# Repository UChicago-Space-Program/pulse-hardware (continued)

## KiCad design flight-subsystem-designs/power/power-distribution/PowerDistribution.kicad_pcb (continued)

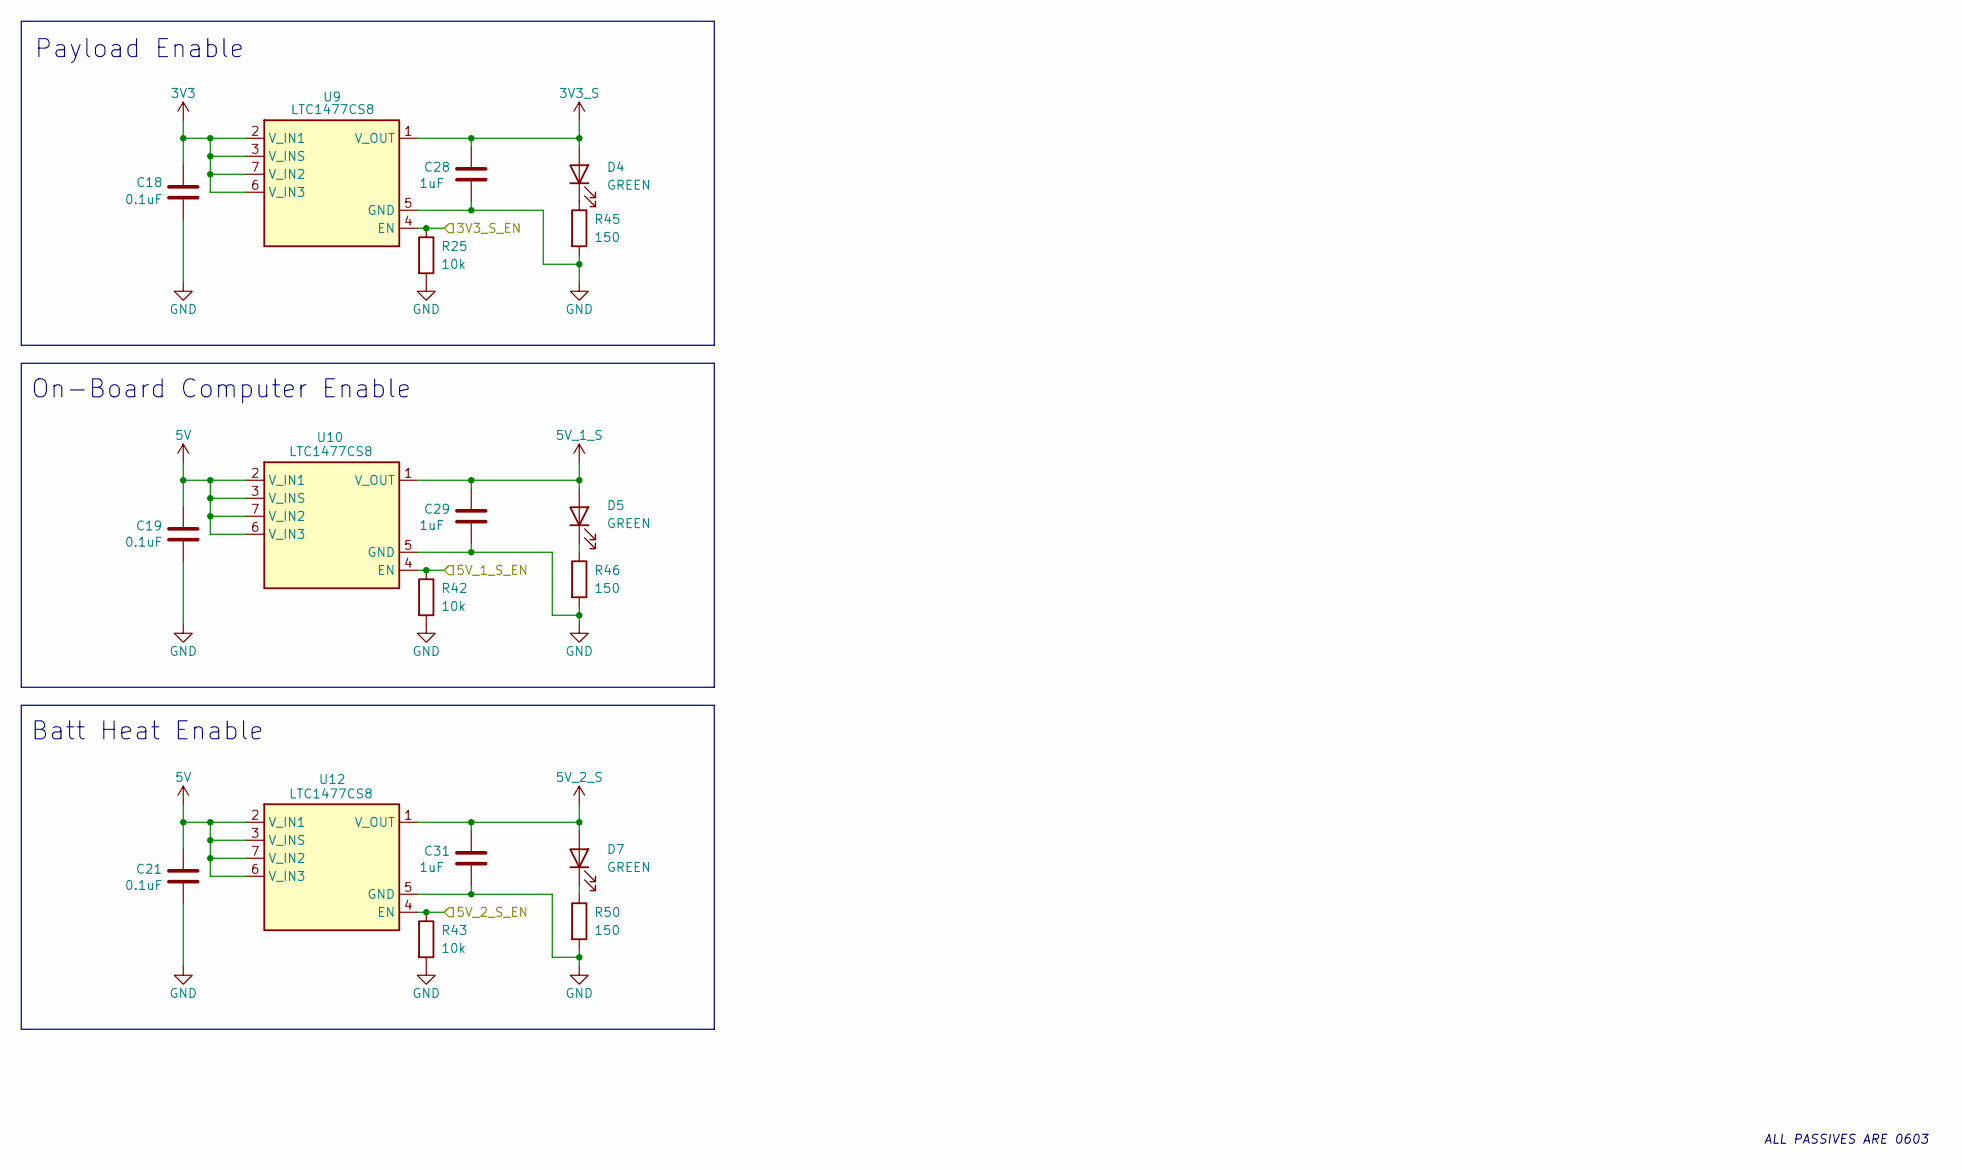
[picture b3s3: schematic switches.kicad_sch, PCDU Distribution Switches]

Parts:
C18, C19, C21: 0.1uF; C_0603_1608Metric
C28, C29, C31: 1uF; C_0603_1608Metric
D4, D5, D7: GREEN; LED_0603_1608Metric
R25, R42, R43: 10k; R_0603_1608Metric
R45, R46, R50: 150; R_0603_1608Metric
U9, U10, U12: LTC1477CS8; SOIC-8_3.9x4.9mm_P1.27mm

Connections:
3V3: C18.1, U9.2 (V_IN1), U9.3 (V_INS), U9.6 (V_IN3), U9.7 (V_IN2); also elsewhere on the board
3V3_S: C28.1, D4.2 (A), U9.1 (V_OUT), U9.8 (V_OUT); also elsewhere on the board
5V: C19.1, C21.1, U10.2 (V_IN1), U10.3 (V_INS), U10.6 (V_IN3), U10.7 (V_IN2), U12.2 (V_IN1), U12.3 (V_INS), U12.6 (V_IN3), U12.7 (V_IN2); also elsewhere on the board
5V_1_S: C29.1, D5.2 (A), U10.1 (V_OUT), U10.8 (V_OUT); also elsewhere on the board
5V_2_S: C31.1, D7.2 (A), U12.1 (V_OUT), U12.8 (V_OUT); also elsewhere on the board
/Control/3V3_S_EN: R25.1, U9.4 (EN); also elsewhere on the board
/Control/5V_1_S_EN: R42.1, U10.4 (EN); also elsewhere on the board
/Control/5V_2_S_EN: R43.1, U12.4 (EN); also elsewhere on the board
GND: C18.2, C19.2, C21.2, C28.2, C29.2, C31.2, R25.2, R42.2, R43.2, R45.2, R46.2, R50.2, U9.5 (GND), U10.5 (GND), U12.5 (GND); also elsewhere on the board
unnamed: D4.1 (K), R45.1
unnamed: D5.1 (K), R46.1
unnamed: D7.1 (K), R50.1

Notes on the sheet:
Payload Enable
Batt Heat Enable
ALL PASSIVES ARE 0603
On-Board Computer Enable

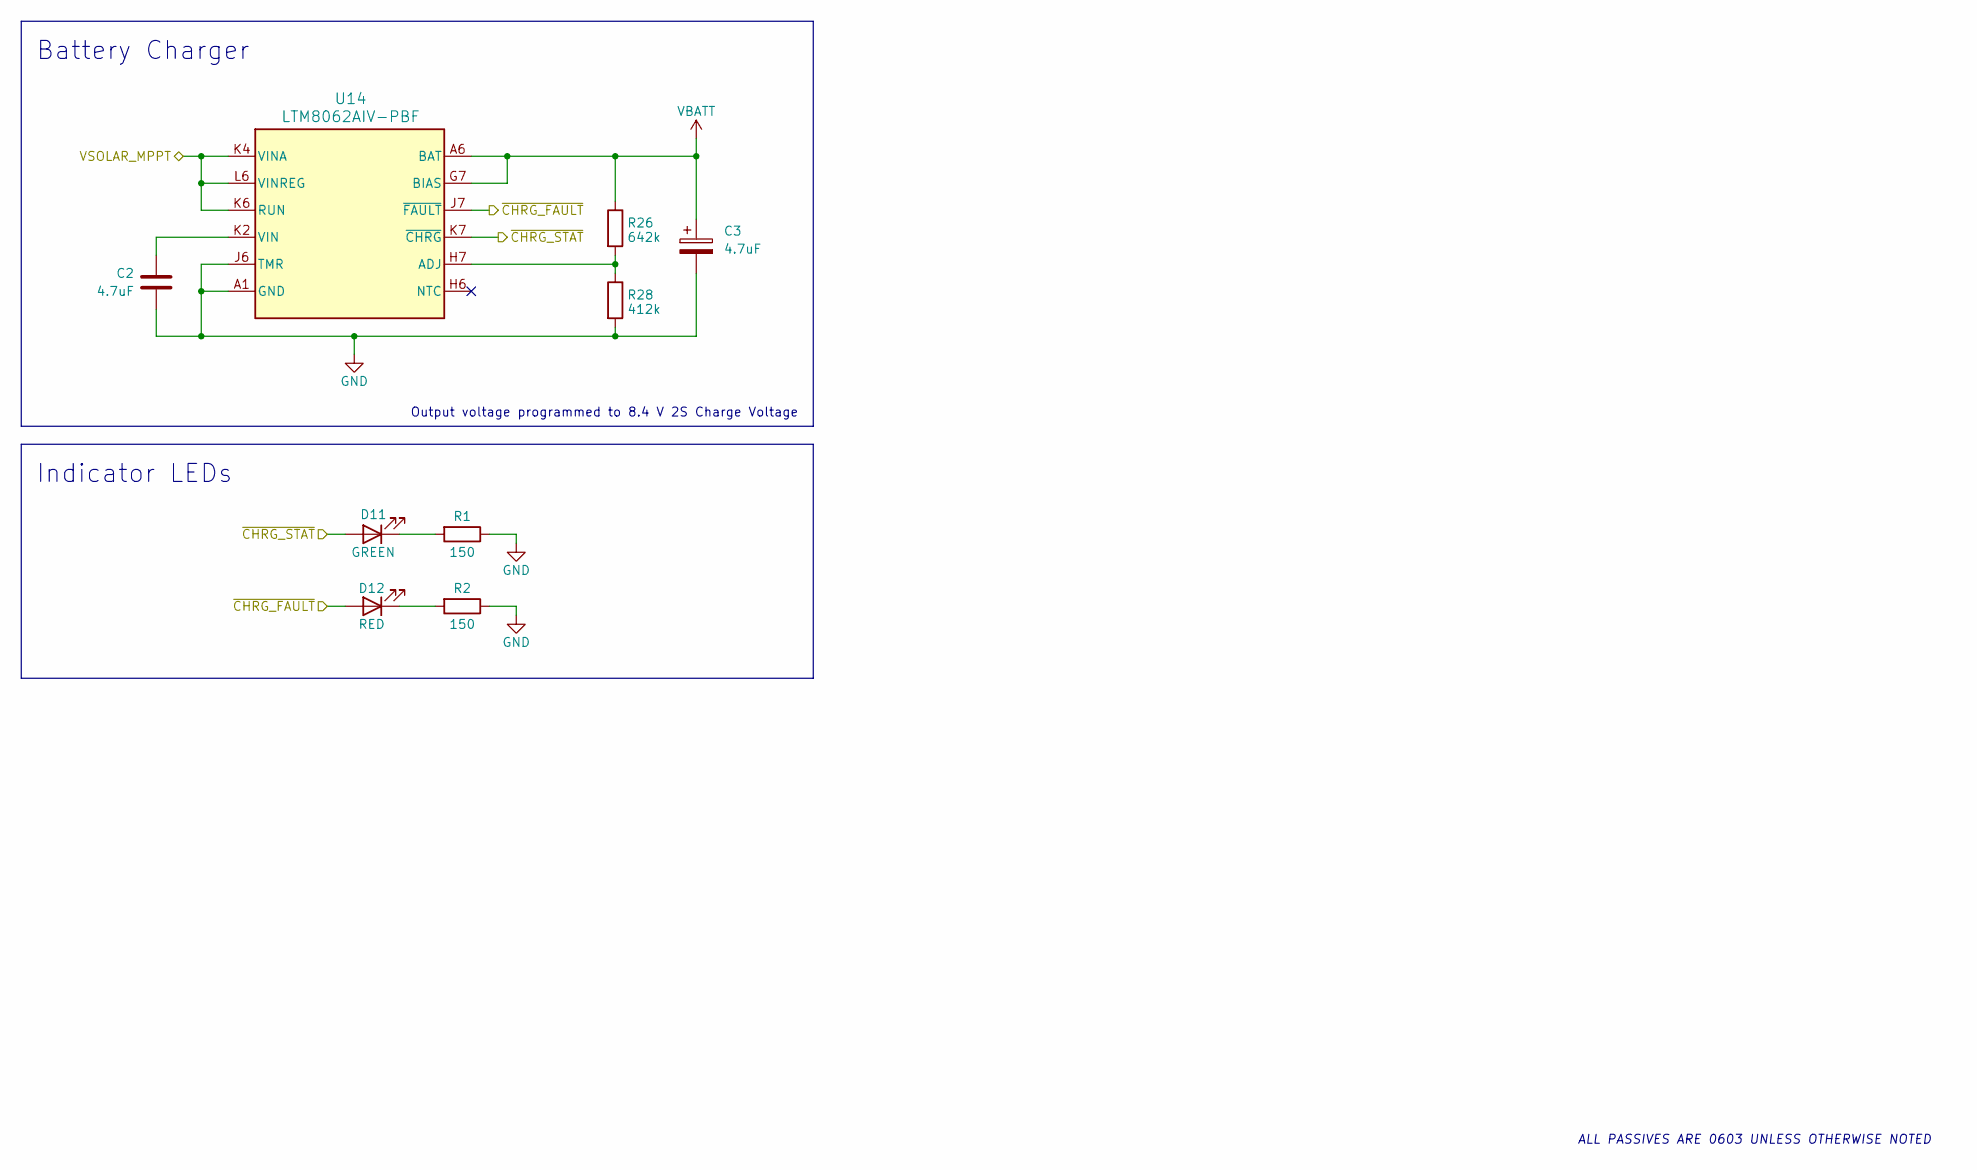
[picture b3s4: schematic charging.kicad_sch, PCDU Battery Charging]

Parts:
C2: 4.7uF; C_1206_3216Metric
C3: 4.7uF; CP_EIA-3528-12_Kemet-T
D11: GREEN; LED_0603_1608Metric
D12: RED; LED_0603_1608Metric
R1, R2: 150; R_0603_1608Metric
R26: 642k; R_0603_1608Metric
R28: 412k; R_0603_1608Metric
U14: LTM8062AIV-PBF; LGA-77_15X9_2_LIT

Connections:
/Charging/~CHRG_FAULT: D12.2 (A), U14.J7 (~FAULT); also elsewhere on the board
/Charging/~CHRG_STAT: D11.2 (A), U14.K7 (~CHRG); also elsewhere on the board
GND: C2.1, C3.2, R1.1, R2.1, R28.2, U14.A1 (GND), U14.A2 (GND), U14.A3 (GND), U14.A4 (GND), U14.A5 (GND), U14.B1 (GND), U14.B2 (GND), U14.B3 (GND), U14.B5 (GND), U14.C1 (GND), U14.C2 (GND), U14.C3 (GND), U14.C4 (GND), U14.C5 (GND), U14.D1 (GND), U14.D2 (GND), U14.D3 (GND), U14.D4 (GND), U14.D5 (GND), U14.F1 (GND), U14.F2 (GND), U14.F3 (GND), U14.F4 (GND), U14.F5 (GND), U14.G1 (GND), U14.G2 (GND), U14.G3 (GND), U14.G4 (GND), U14.G5 (GND), U14.G6 (GND), U14.H1 (GND), U14.H2 (GND), U14.H3 (GND), U14.H4 (GND), U14.H5 (GND), U14.J1 (GND), U14.J2 (GND), U14.J3 (GND), U14.J4 (GND), U14.J5 (GND), U14.J6 (TMR), U14.L7 (GND); also elsewhere on the board
unnamed: C2.2, U14.K1 (VIN), U14.K2 (VIN), U14.K3 (VIN), U14.L1 (VIN), U14.L2 (VIN), U14.L3 (VIN)
unnamed: D11.1 (K), R1.2
unnamed: D12.1 (K), R2.2
unnamed: R26.2, R28.1, U14.H7 (ADJ)
VBATT: C3.1, R26.1, U14.A6 (BAT), U14.A7 (BAT), U14.B6 (BAT), U14.B7 (BAT), U14.C6 (BAT), U14.C7 (BAT), U14.D6 (BAT), U14.D7 (BAT), U14.E6 (BAT), U14.E7 (BAT), U14.F6 (BAT), U14.F7 (BAT), U14.G7 (BIAS); also elsewhere on the board
VINA: U14.K4 (VINA), U14.K5 (VINA), U14.K6 (RUN), U14.L4 (VINA), U14.L5 (VINA), U14.L6 (VINREG); also elsewhere on the board

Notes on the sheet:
ALL PASSIVES ARE 0603 UNLESS OTHERWISE NOTED
Battery Charger
Indicator LEDs
Output voltage programmed to 8.4 V 2S Charge Voltage

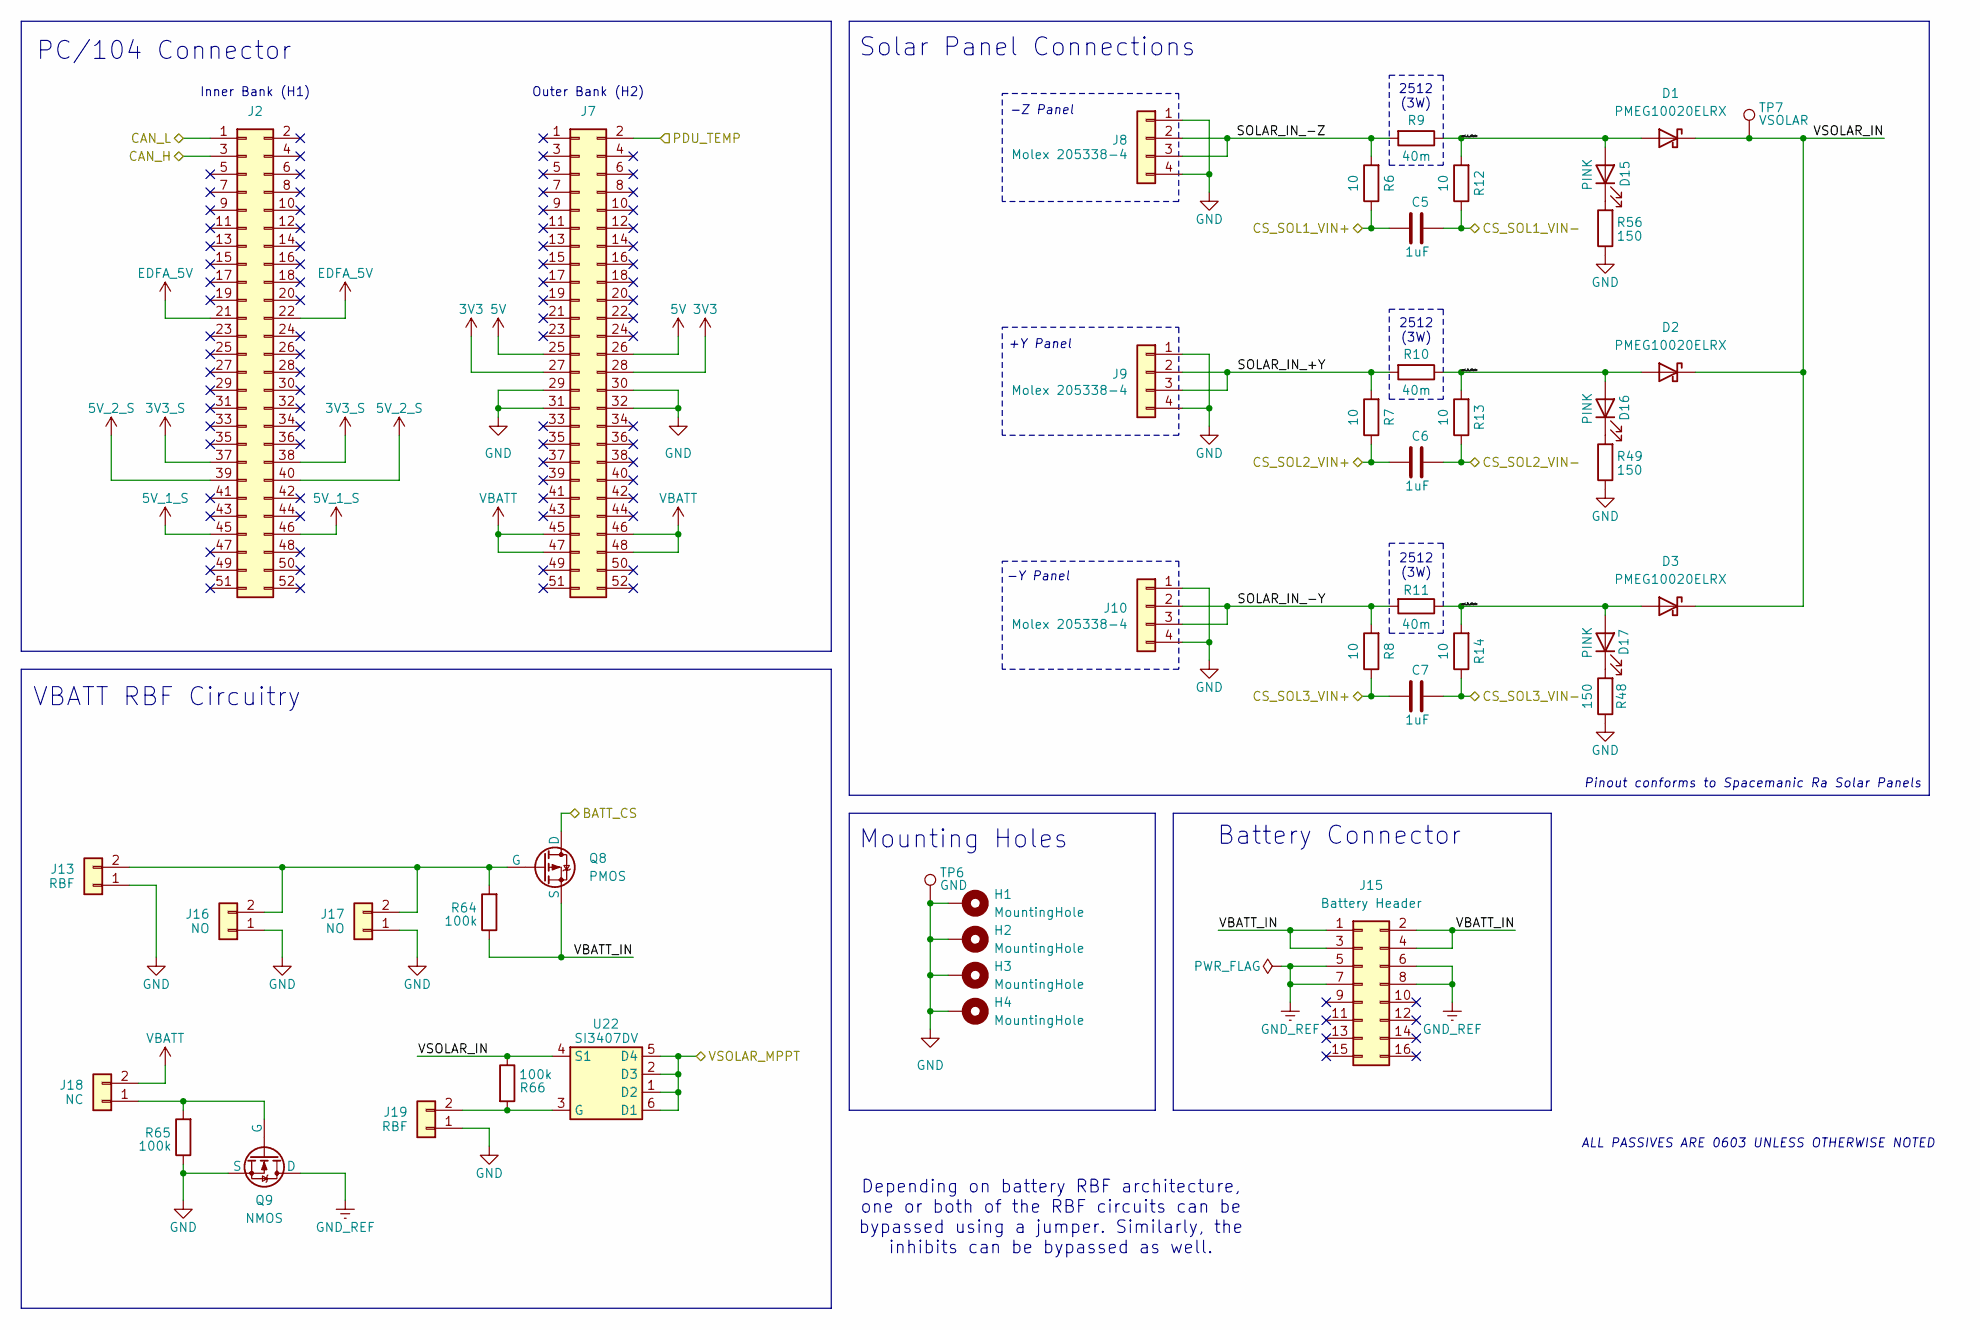
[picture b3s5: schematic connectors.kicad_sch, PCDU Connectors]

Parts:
C5, C6, C7: 1uF; C_0603_1608Metric
D1, D2, D3: PMEG10020ELRX; Nexperia_CFP3_SOD-123W
D15, D16, D17: PINK; LED_0603_1608Metric
H1, H2, H3, H4: MountingHole; MountingHole_3.2mm_M3_Pad_TopBottom
J2, J7: Conn_02x26_Odd_Even; PinHeader_2x26_P2.54mm_Vertical
J8, J9, J10: Molex 205338-4; Molex_PicoBlade_53047-0410_1x04_P1.25mm_Vertical
J13, J19: RBF; Molex_PicoBlade_53047-0210_1x02_P1.25mm_Vertical
J15: Battery Header; PinHeader_2x08_P2.54mm_Vertical
J16, J17: NO; Molex_PicoBlade_53047-0210_1x02_P1.25mm_Vertical
J18: NC; Molex_PicoBlade_53047-0210_1x02_P1.25mm_Vertical
Q8: PMOS; TSOP-6_1.65x3.05mm_P0.95mm
Q9: NMOS; TSOP-6_1.65x3.05mm_P0.95mm
R6, R7, R8, R12, R13, R14: 10; R_0603_1608Metric
R9, R10, R11: 40m; R_2512_6332Metric
R48, R49, R56: 150; R_0603_1608Metric
R64, R65, R66: 100k; R_0603_1608Metric
TP6: GND; TestPoint_Keystone_5000-5004_Miniature
TP7: VSOLAR; TestPoint_Keystone_5000-5004_Miniature
U22: SI3407DV; TSOP-6_1.65x3.05mm_P0.95mm

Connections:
3V3: J7.27, J7.28; also elsewhere on the board
3V3_S: J2.37, J2.38; also elsewhere on the board
5V: J7.25, J7.26; also elsewhere on the board
5V_1_S: J2.45, J2.46; also elsewhere on the board
5V_2_S: J2.39, J2.40; also elsewhere on the board
/Connectors/BATT_CS: Q8.1 (D), Q8.2 (D), Q8.5 (D), Q8.6 (D); also elsewhere on the board
/Connectors/CAN_H: J2.3; also elsewhere on the board
/Connectors/CAN_L: J2.1; also elsewhere on the board
/Connectors/CS_SOL1_VIN+: C5.2, R6.1; also elsewhere on the board
/Connectors/CS_SOL1_VIN-: C5.1, R12.1; also elsewhere on the board
/Connectors/CS_SOL2_VIN+: C6.2, R7.1; also elsewhere on the board
/Connectors/CS_SOL2_VIN-: C6.1, R13.1; also elsewhere on the board
/Connectors/CS_SOL3_VIN+: C7.2, R8.1; also elsewhere on the board
/Connectors/CS_SOL3_VIN-: C7.1, R14.1; also elsewhere on the board
/Connectors/PDU_TEMP: J7.2; also elsewhere on the board
/Connectors/SOLAR_IN_+Y: J9.2, J9.3, R7.2, R10.2
/Connectors/SOLAR_IN_-Y: J10.2, J10.3, R8.2, R11.2
/Connectors/SOLAR_IN_-Z: J8.2, J8.3, R6.2, R9.2
/Connectors/VBATT_IN: J15.1, J15.2, J15.3, J15.4, Q8.4 (S), R64.1
/Connectors/VSOLAR_IN: D1.1 (K), D2.1 (K), D3.1 (K), R66.1, TP7.1, U22.4 (S1)
/Connectors/sol_1_diode: D1.2 (A), D15.2 (A), R9.1, R12.2
/Connectors/sol_2_diode: D2.2 (A), D16.2 (A), R10.1, R13.2
/Connectors/sol_3_diode: D3.2 (A), D17.2 (A), R11.1, R14.2
EDFA_5V: J2.21, J2.22; also elsewhere on the board
GND: H1.MP, H2.MP, H3.MP, H4.MP, J7.29, J7.30, J7.31, J7.32, J8.1, J8.4, J9.1, J9.4, J10.1, J10.4, J13.1, J16.1, J17.1, J19.1, Q9.3 (S), R48.1, R49.1, R56.1, R65.1, TP6.1; also elsewhere on the board
GND_REF: J15.5, J15.6, J15.7, J15.8, Q9.1 (D)
unnamed: D15.1 (K), R56.2
unnamed: D16.1 (K), R49.2
unnamed: D17.1 (K), R48.2
unnamed: J13.2, J16.2, J17.2, Q8.3 (G), R64.2
unnamed: J18.1, Q9.2 (G), R65.2
unnamed: J19.2, R66.2, U22.3 (G)
VBATT: J7.45, J7.46, J7.47, J7.48, J18.2; also elsewhere on the board
VINA: U22.1 (D2), U22.2 (D3), U22.5 (D4), U22.6 (D1); also elsewhere on the board

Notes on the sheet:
2512 (3W)
PC/104 Connector
Inner Bank (H1)
-Z Panel
Mounting Holes
Solar Panel Connections
Pinout conforms to Spacemanic Ra Solar Panels
+Y Panel
-Y Panel
Battery Connector
VBATT RBF Circuitry
ALL PASSIVES ARE 0603 UNLESS OTHERWISE NOTED
Depending on battery RBF architecture, one or both of the RBF circuits can be bypassed using a jumper. Similarly, the inhibits can be bypassed as well.
Outer Bank (H2)

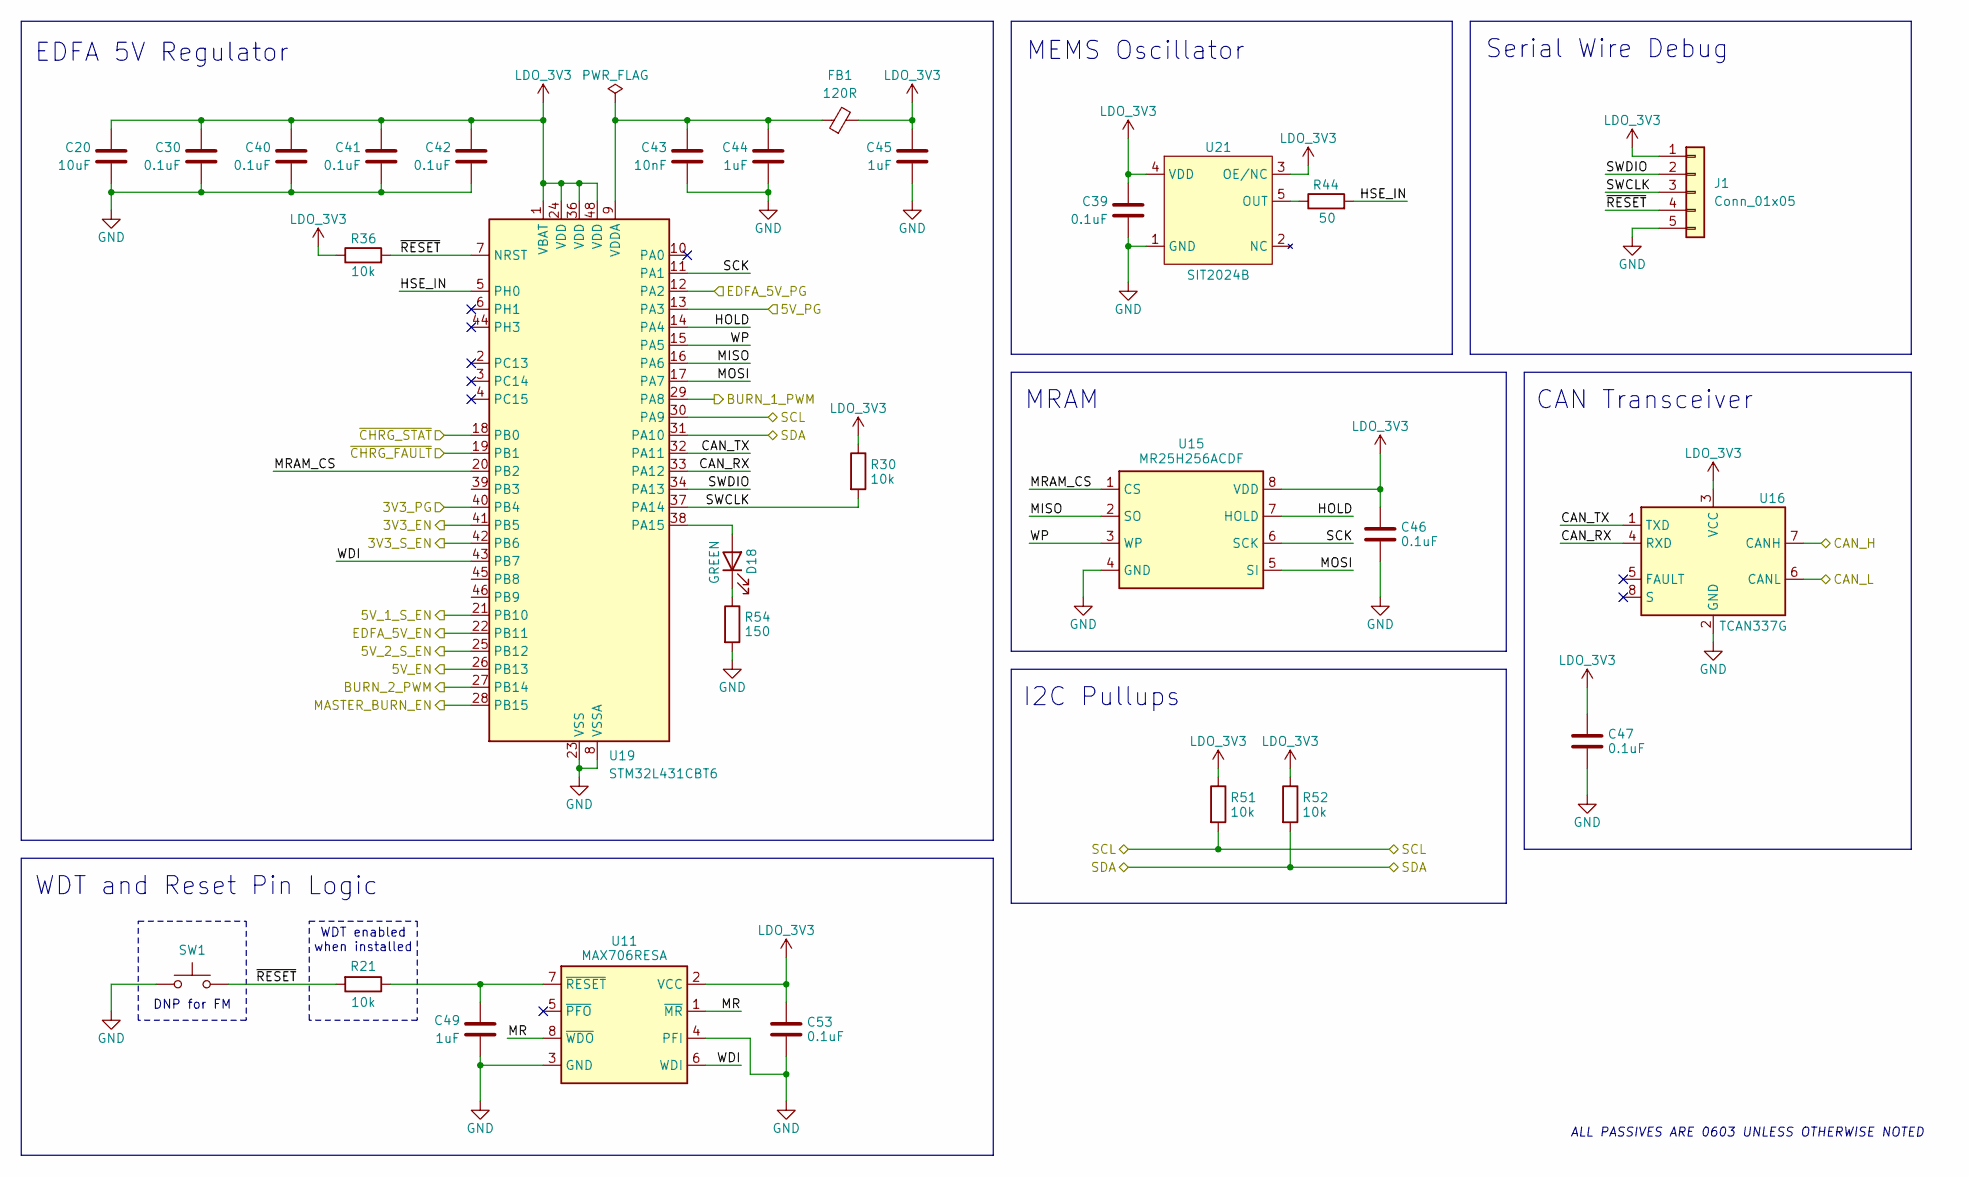
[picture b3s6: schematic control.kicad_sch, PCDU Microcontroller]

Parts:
C20: 10uF; C_0603_1608Metric
C30, C39, C40, C41, C42, C46, C47, C53: 0.1uF; C_0603_1608Metric
C43: 10nF; C_0603_1608Metric
C44, C45, C49: 1uF; C_0603_1608Metric
D18: GREEN; LED_0603_1608Metric
FB1: 120R; L_0805_2012Metric
J1: Conn_01x05; Molex_PicoBlade_53047-0510_1x05_P1.25mm_Vertical
R21, R30, R36, R51, R52: 10k; R_0603_1608Metric
R44: 50; R_0603_1608Metric
R54: 150; R_0603_1608Metric
SW1: SW_Push; SW_SPST_B3U-1000P
U11: MAX706RESA; SOIC-8_3.9x4.9mm_P1.27mm
U15: MR25H256ACDF; DFN-8-1EP_6x5mm_P1.27mm_EP2x2mm
U16: TCAN337G; SOIC-8_3.9x4.9mm_P1.27mm
U19: STM32L431CBT6; LQFP-48_7x7mm_P0.5mm
U21: SIT2024B; SOT-23-5

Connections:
/Charging/~CHRG_FAULT: U19.18 (PB0); also elsewhere on the board
/Charging/~CHRG_STAT: U19.19 (PB1); also elsewhere on the board
/Connectors/CAN_H: U16.7 (CANH); also elsewhere on the board
/Connectors/CAN_L: U16.6 (CANL); also elsewhere on the board
/Control/3V3_EN: U19.41 (PB5); also elsewhere on the board
/Control/3V3_PG: U19.40 (PB4); also elsewhere on the board
/Control/3V3_S_EN: U19.42 (PB6); also elsewhere on the board
/Control/5V_1_S_EN: U19.21 (PB10); also elsewhere on the board
/Control/5V_2_S_EN: U19.25 (PB12); also elsewhere on the board
/Control/5V_EN: U19.26 (PB13); also elsewhere on the board
/Control/5V_PG: U19.13 (PA3); also elsewhere on the board
/Control/BURN_1_PWM: U19.29 (PA8); also elsewhere on the board
/Control/BURN_2_PWM: U19.27 (PB14); also elsewhere on the board
/Control/CAN_RX: U16.4 (RXD), U19.33 (PA12)
/Control/CAN_TX: U16.1 (TXD), U19.32 (PA11)
/Control/EDFA_5V_EN: U19.22 (PB11); also elsewhere on the board
/Control/EDFA_5V_PG: U19.12 (PA2); also elsewhere on the board
/Control/HOLD: U15.7 (HOLD), U19.14 (PA4)
/Control/HSE_IN: R44.2, U19.5 (PH0)
/Control/MASTER_BURN_EN: U19.28 (PB15); also elsewhere on the board
/Control/MISO: U15.2 (SO), U19.16 (PA6)
/Control/MOSI: U15.5 (SI), U19.17 (PA7)
/Control/MR: U11.1 (~MR), U11.8 (~WDO)
/Control/MRAM_CS: U15.1 (CS), U19.20 (PB2)
/Control/SCK: U15.6 (SCK), U19.11 (PA1)
/Control/SCL: R51.2, U19.30 (PA9); also elsewhere on the board
/Control/SDA: R52.2, U19.31 (PA10); also elsewhere on the board
/Control/SWCLK: J1.3, R30.2, U19.37 (PA14)
/Control/SWDIO: J1.2, U19.34 (PA13)
/Control/WDI: U11.6 (WDI), U19.43 (PB7)
/Control/WP: U15.3 (WP), U19.15 (PA5)
/Control/~RESET: J1.4, R21.2, R36.2, SW1.2, U19.7 (NRST)
GND: C20.2, C30.2, C39.2, C40.2, C41.2, C42.2, C43.2, C44.2, C45.2, C46.1, C47.1, C49.2, C53.1, J1.5, R54.2, SW1.1, U11.3 (GND), U11.4 (PFI), U15.4 (GND), U16.2 (GND), U19.8 (VSSA), U19.23 (VSS), U19.35 (VSS), U19.47 (VSS), U21.1 (GND); also elsewhere on the board
LDO_3V3: C20.1, C30.1, C39.1, C40.1, C41.1, C42.1, C45.1, C46.2, C47.2, C53.2, FB1.2, J1.1, R30.1, R36.1, R51.1, R52.1, U11.2 (VCC), U15.8 (VDD), U16.3 (VCC), U19.1 (VBAT), U19.24 (VDD), U19.36 (VDD), U19.48 (VDD), U21.3 (OE/NC), U21.4 (VDD); also elsewhere on the board
unnamed: D18.2 (A), U19.38 (PA15)
unnamed: D18.1 (K), R54.1
unnamed: C49.1, R21.1, U11.7 (~RESET)
unnamed: C43.1, C44.1, FB1.1, U19.9 (VDDA)
unnamed: R44.1, U21.5 (OUT)

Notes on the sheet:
EDFA 5V Regulator
Serial Wire Debug
MEMS Oscillator
ALL PASSIVES ARE 0603 UNLESS OTHERWISE NOTED
WDT and Reset Pin Logic
CAN Transceiver
I2C Pullups
WDT enabled when installed
MRAM
DNP for FM

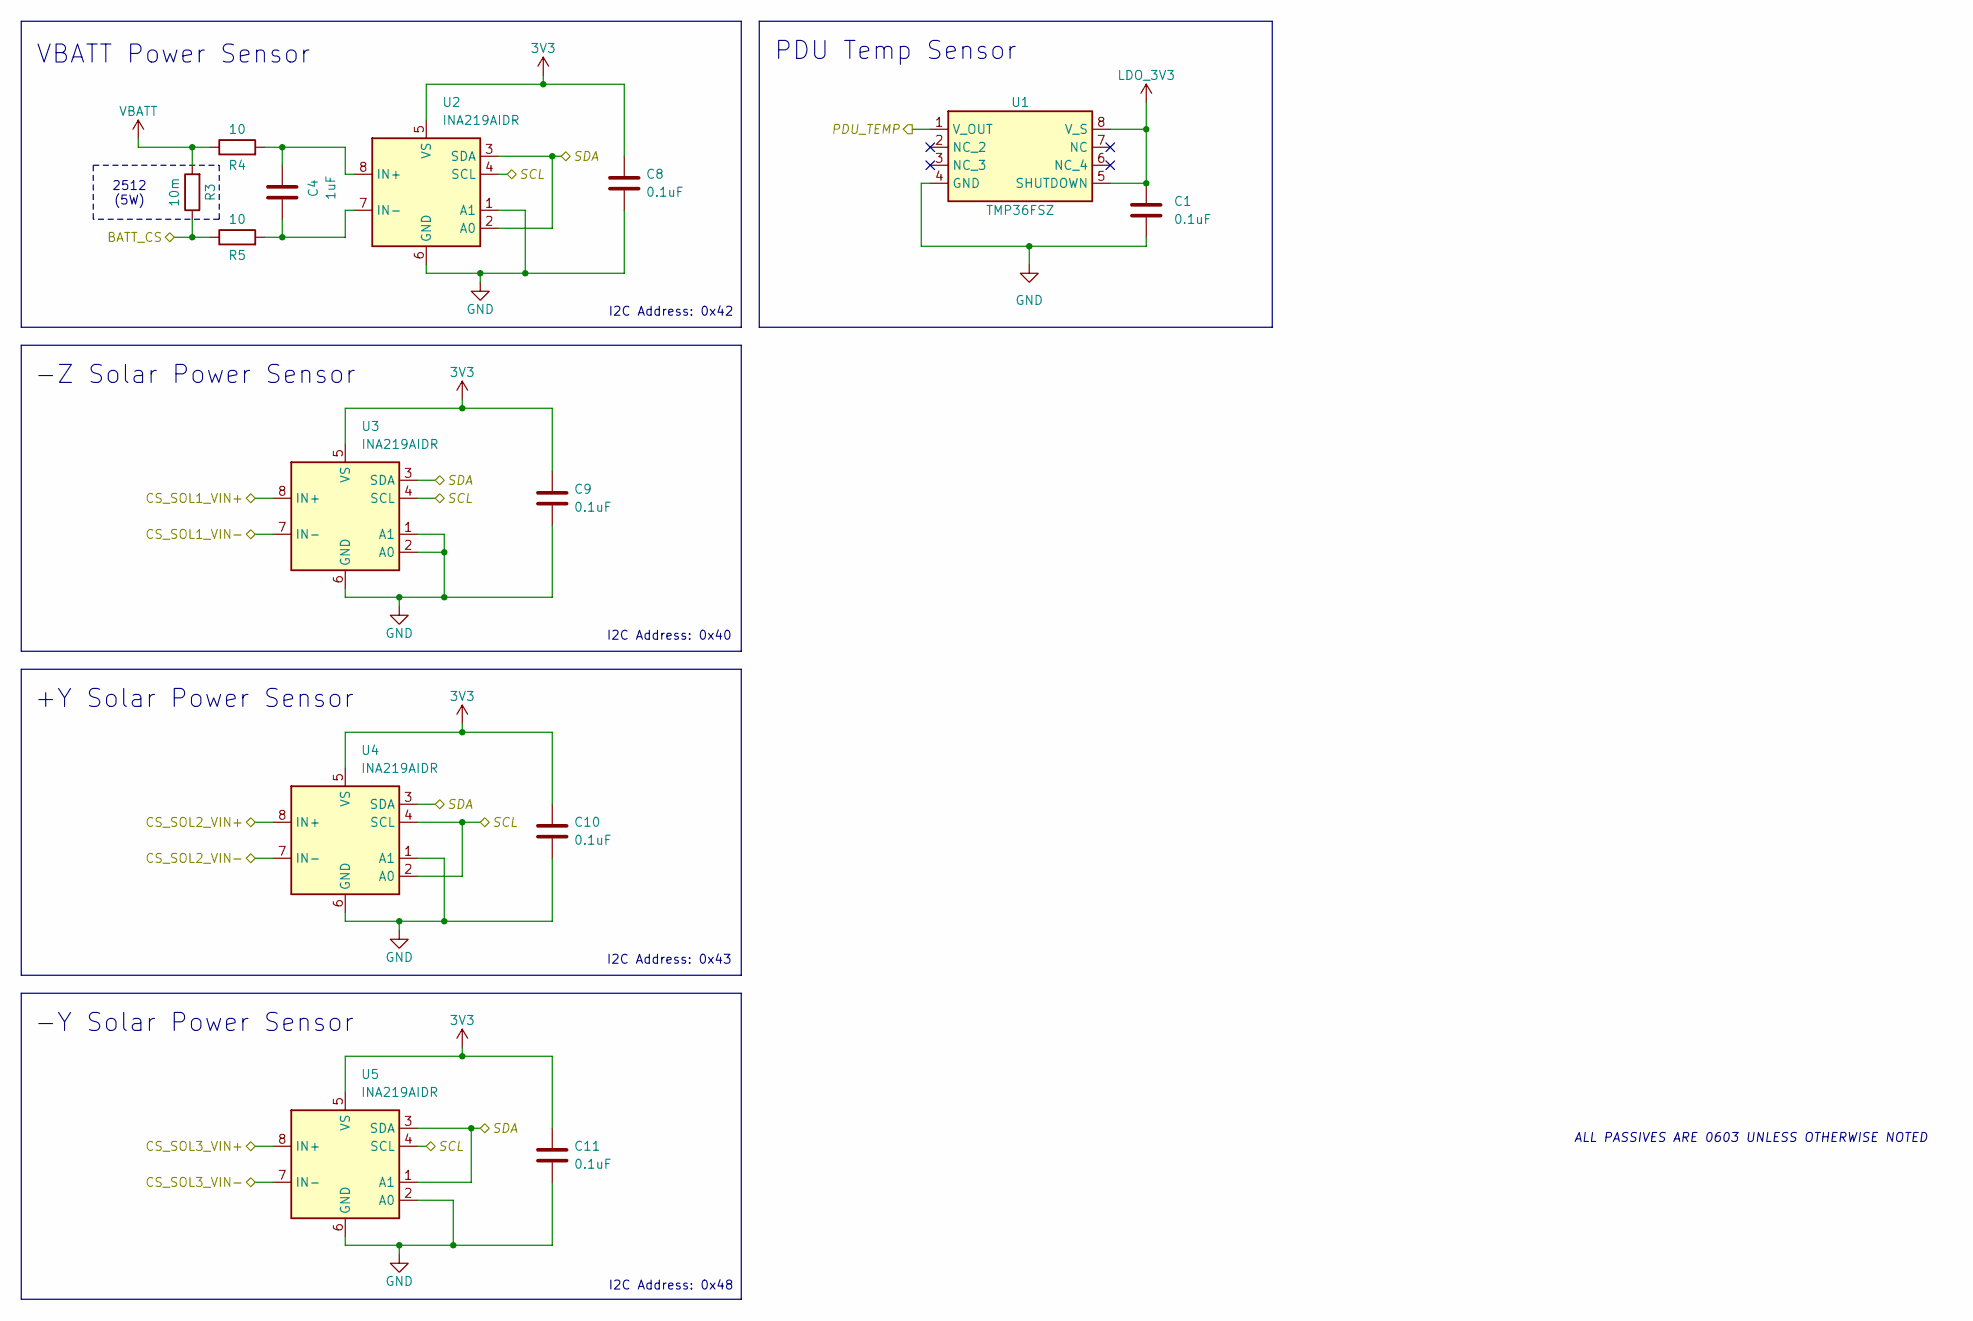
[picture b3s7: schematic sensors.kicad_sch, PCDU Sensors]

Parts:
C1, C8, C9, C10, C11: 0.1uF; C_0603_1608Metric
C4: 1uF; C_0603_1608Metric
R3: 10m; R_2512_6332Metric
R4, R5: 10; R_0603_1608Metric
U1: TMP36FSZ; SOIC-8-1EP_3.9x4.9mm_P1.27mm_EP2.41x3.3mm
U2, U3, U4, U5: INA219AIDR; SOIC-8_3.9x4.9mm_P1.27mm

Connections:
3V3: C8.2, C9.2, C10.2, C11.2, U2.5 (VS), U3.5 (VS), U4.5 (VS), U5.5 (VS); also elsewhere on the board
/Connectors/BATT_CS: R3.1, R5.1; also elsewhere on the board
/Connectors/CS_SOL1_VIN+: U3.8 (IN+); also elsewhere on the board
/Connectors/CS_SOL1_VIN-: U3.7 (IN-); also elsewhere on the board
/Connectors/CS_SOL2_VIN+: U4.8 (IN+); also elsewhere on the board
/Connectors/CS_SOL2_VIN-: U4.7 (IN-); also elsewhere on the board
/Connectors/CS_SOL3_VIN+: U5.8 (IN+); also elsewhere on the board
/Connectors/CS_SOL3_VIN-: U5.7 (IN-); also elsewhere on the board
/Connectors/PDU_TEMP: U1.1 (V_OUT); also elsewhere on the board
/Control/SCL: U2.4 (SCL), U3.4 (SCL), U4.2 (A0), U4.4 (SCL), U5.4 (SCL); also elsewhere on the board
/Control/SDA: U2.2 (A0), U2.3 (SDA), U3.3 (SDA), U4.3 (SDA), U5.1 (A1), U5.3 (SDA); also elsewhere on the board
GND: C1.1, C8.1, C9.1, C10.1, C11.1, U1.4 (GND), U2.1 (A1), U2.6 (GND), U3.1 (A1), U3.2 (A0), U3.6 (GND), U4.1 (A1), U4.6 (GND), U5.2 (A0), U5.6 (GND); also elsewhere on the board
LDO_3V3: C1.2, U1.5 (SHUTDOWN), U1.8 (V_S); also elsewhere on the board
unnamed: C4.1, R4.2, U2.8 (IN+)
unnamed: C4.2, R5.2, U2.7 (IN-)
VBATT: R3.2, R4.1; also elsewhere on the board

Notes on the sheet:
VBATT Power Sensor
I2C Address: 0x43
PDU Temp Sensor
I2C Address: 0x42
+Y Solar Power Sensor
I2C Address: 0x48
-Y Solar Power Sensor
2512 (5W)
I2C Address: 0x40
-Z Solar Power Sensor
ALL PASSIVES ARE 0603 UNLESS OTHERWISE NOTED

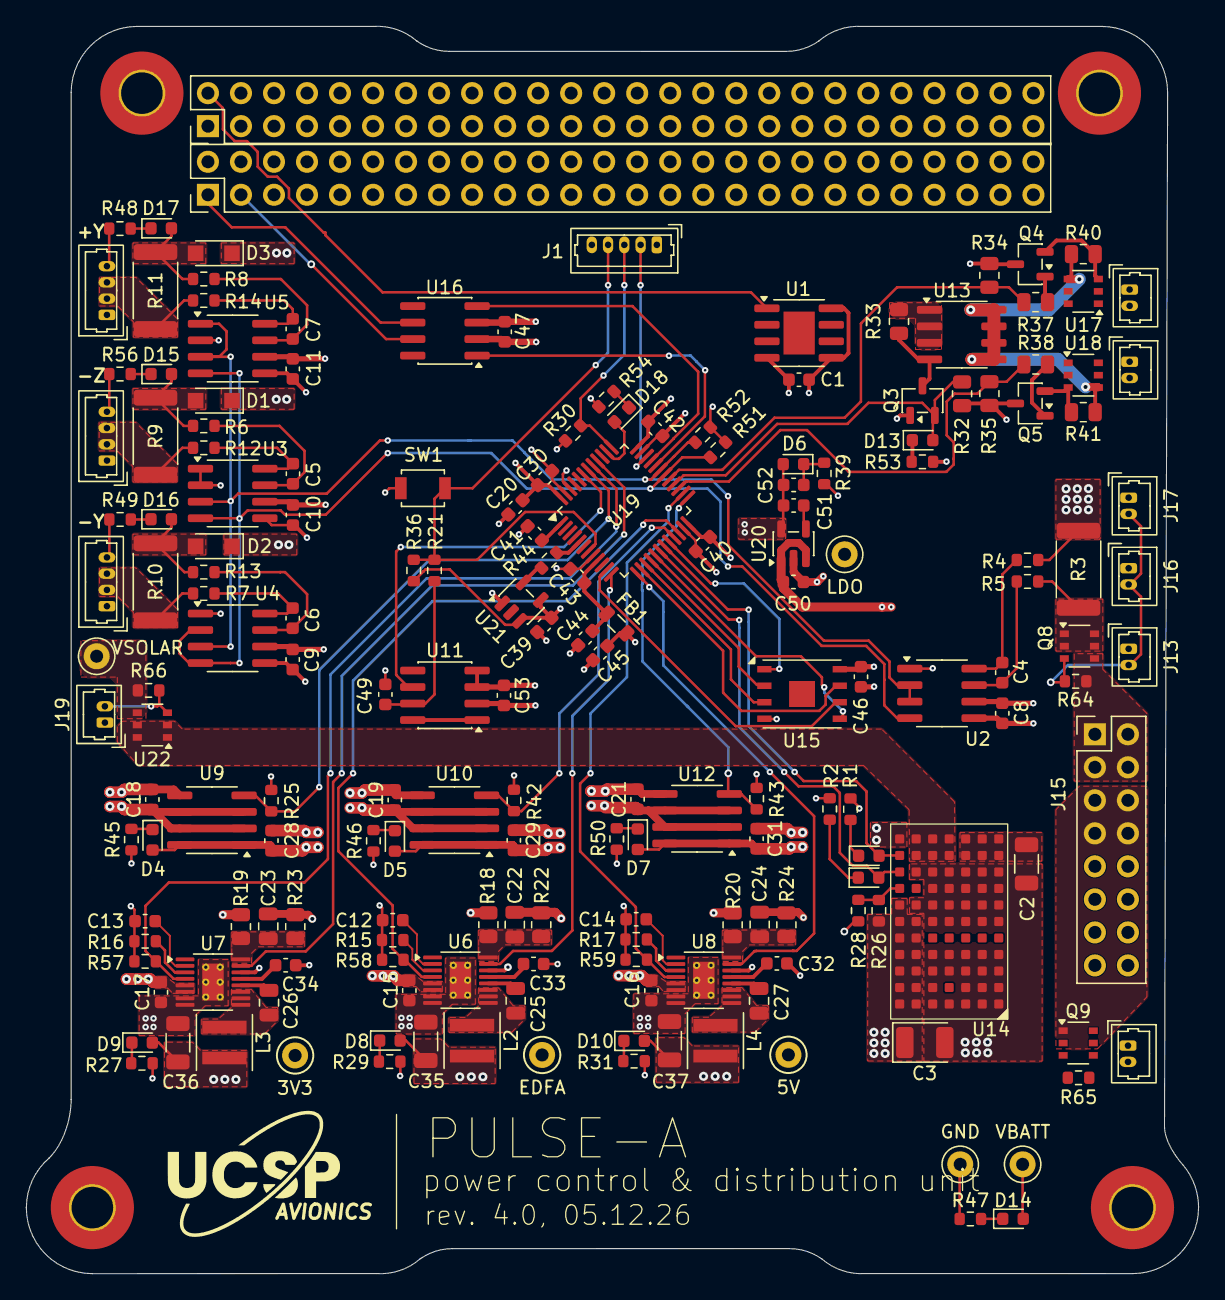
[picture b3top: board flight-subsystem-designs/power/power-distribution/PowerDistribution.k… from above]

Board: 4 copper layers, 90.2 x 96.0 mm, 187 parts (0 on the bottom side), 112 nets.
